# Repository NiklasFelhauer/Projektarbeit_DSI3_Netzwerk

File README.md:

# Projektarbeit_DSI3_Netzwerk
Umsetzung eines DSI3 Netzwerkes zwischen ESP32-Mikrocontrollern

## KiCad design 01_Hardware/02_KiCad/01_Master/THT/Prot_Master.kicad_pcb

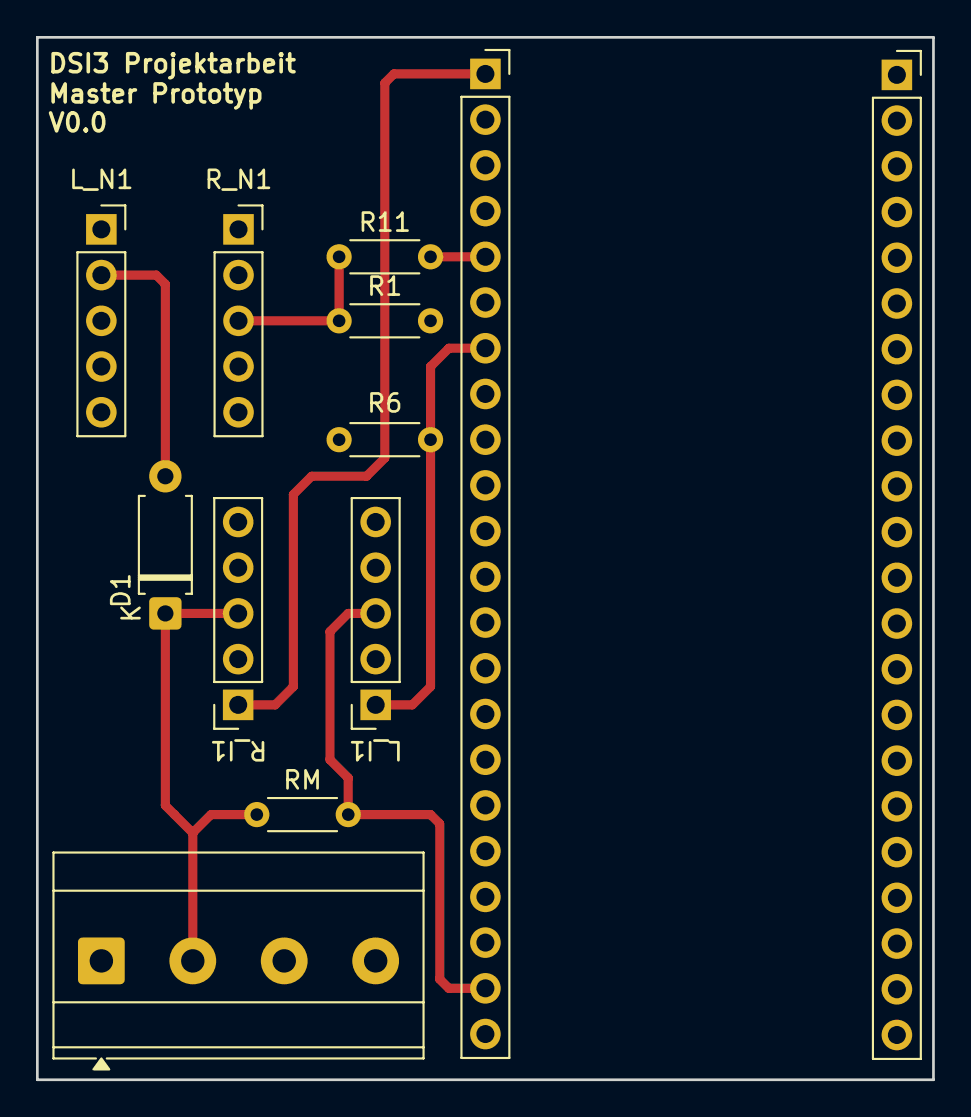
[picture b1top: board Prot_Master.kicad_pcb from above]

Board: 2 copper layers, 49.8 x 57.9 mm, 12 parts (0 on the bottom side), 8 nets.

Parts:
D1: BZX384xxxx; D_A-405_P7.62mm_Horizontal
J5: Screw_Terminal_01x04; TerminalBlock_Phoenix_MKDS-3-4-5.08_1x04_P5.08mm_Horizontal
J10, J20: Conn_01x22_Female; PinSocket_1x22_P2.54mm_Vertical
L_I1: NMOS1; PinSocket_1x05_P2.54mm_Vertical
L_N1: NMOS1; PinSocket_1x05_P2.54mm_Vertical
R1, R6: 10k; R_Axial_DIN0204_L3.6mm_D1.6mm_P5.08mm_Horizontal
R11: 33; R_Axial_DIN0204_L3.6mm_D1.6mm_P5.08mm_Horizontal
RM: 10; R_Axial_DIN0204_L3.6mm_D1.6mm_P5.08mm_Horizontal
R_I1: NMOS2; PinSocket_1x05_P2.54mm_Vertical
R_N1: NMOS1; PinSocket_1x05_P2.54mm_Vertical

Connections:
3.3V: J10.1, R_I1.1
5V: J10.21, L_I1.3, RM.2
Bus: D1.1 (K), J5.2, RM.1, R_I1.3
Drain_N1: D1.2 (A), L_N1.2 (Pin_2_2)
GND: J5.3, J10.22, L_I1.2, R1.2, R6.2, R_N1.1
GPIO: J10.7, L_I1.1, R6.1
Gate_N1: R1.1, R11.1, R_N1.3
unnamed: J10.5, R11.2

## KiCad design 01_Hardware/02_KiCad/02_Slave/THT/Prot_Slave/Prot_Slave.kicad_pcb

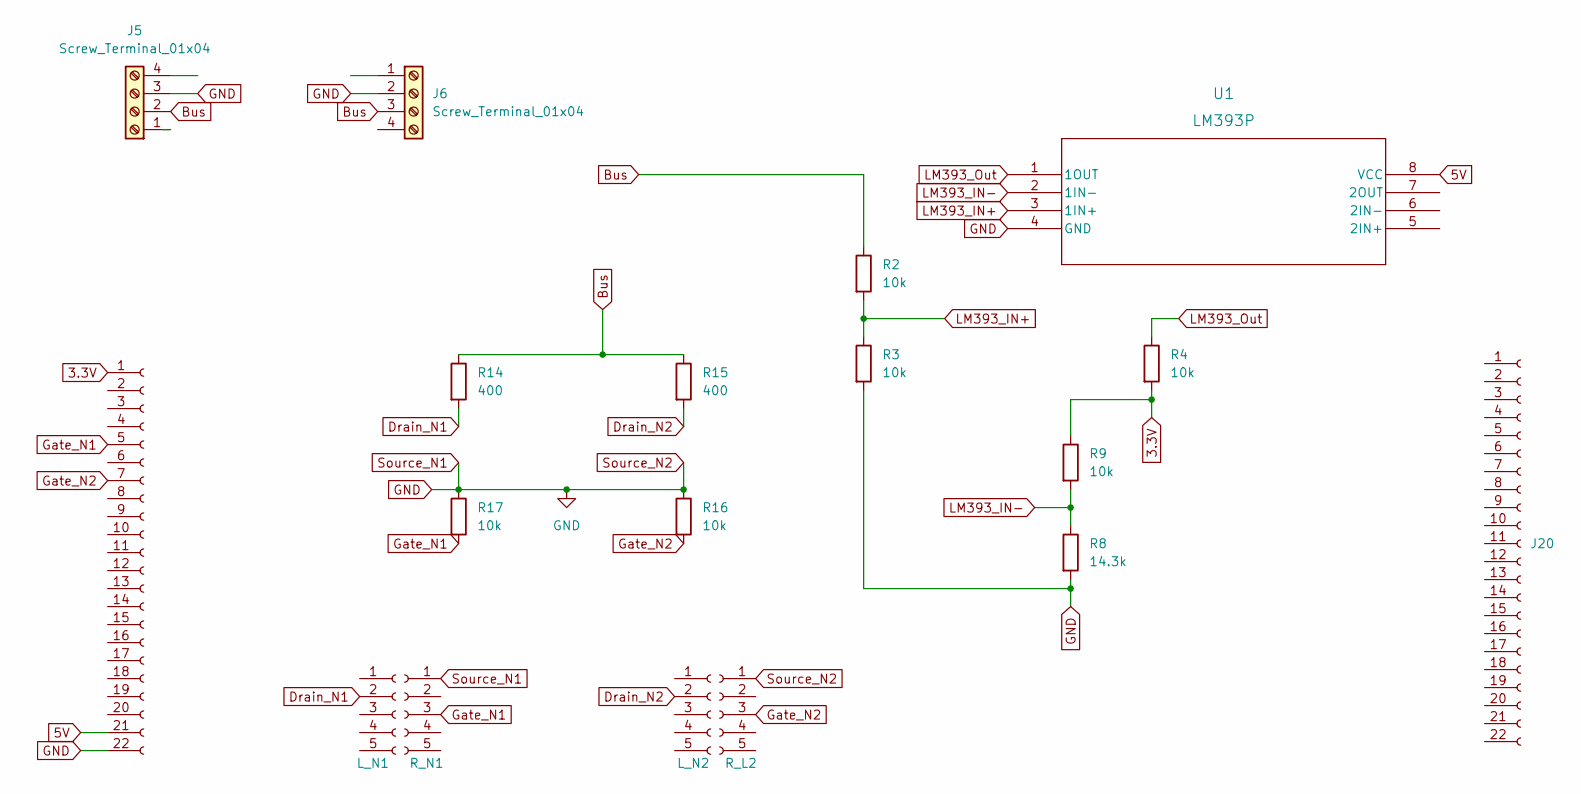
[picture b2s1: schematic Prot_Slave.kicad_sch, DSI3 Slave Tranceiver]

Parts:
J5, J6: Screw_Terminal_01x04; TerminalBlock_Phoenix_MKDS-3-4-5.08_1x04_P5.08mm_Horizontal
J10, J20: Conn_01x22_Female; PinSocket_1x22_P2.54mm_Vertical
L_N1, L_N2: NMOS1; PinSocket_1x05_P2.54mm_Vertical
R2, R3, R4, R9, R16, R17: 10k; R_Axial_DIN0204_L3.6mm_D1.6mm_P5.08mm_Horizontal
R8: 14.3k; R_Axial_DIN0204_L3.6mm_D1.6mm_P5.08mm_Horizontal
R14, R15: 400; R_Axial_DIN0204_L3.6mm_D1.6mm_P5.08mm_Horizontal
R_L2: NMOS2; PinSocket_1x05_P2.54mm_Vertical
R_N1: NMOS1; PinSocket_1x05_P2.54mm_Vertical
U1: LM393P; P8

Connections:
3.3V: J10.1, R4.2, R9.1
5V: J10.21, U1.8 (VCC)
Bus: J5.2, J6.3, R2.1, R14.1, R15.1
Drain_N1: L_N1.2 (Pin_2_2), R14.2
Drain_N2: L_N2.2 (Pin_2_2), R15.2
GND: J5.3, J6.2, J10.22, R3.2, R8.2, R16.1, R17.1, R_L2.1, R_N1.1, U1.4 (GND)
Gate_N1: J10.5, R17.2, R_N1.3
Gate_N2: J10.7, R16.2, R_L2.3
LM393_IN+: R2.2, R3.1, U1.3 (1IN+)
LM393_IN-: R8.1, R9.2, U1.2 (1IN-)
LM393_Out: R4.1, U1.1 (1OUT)

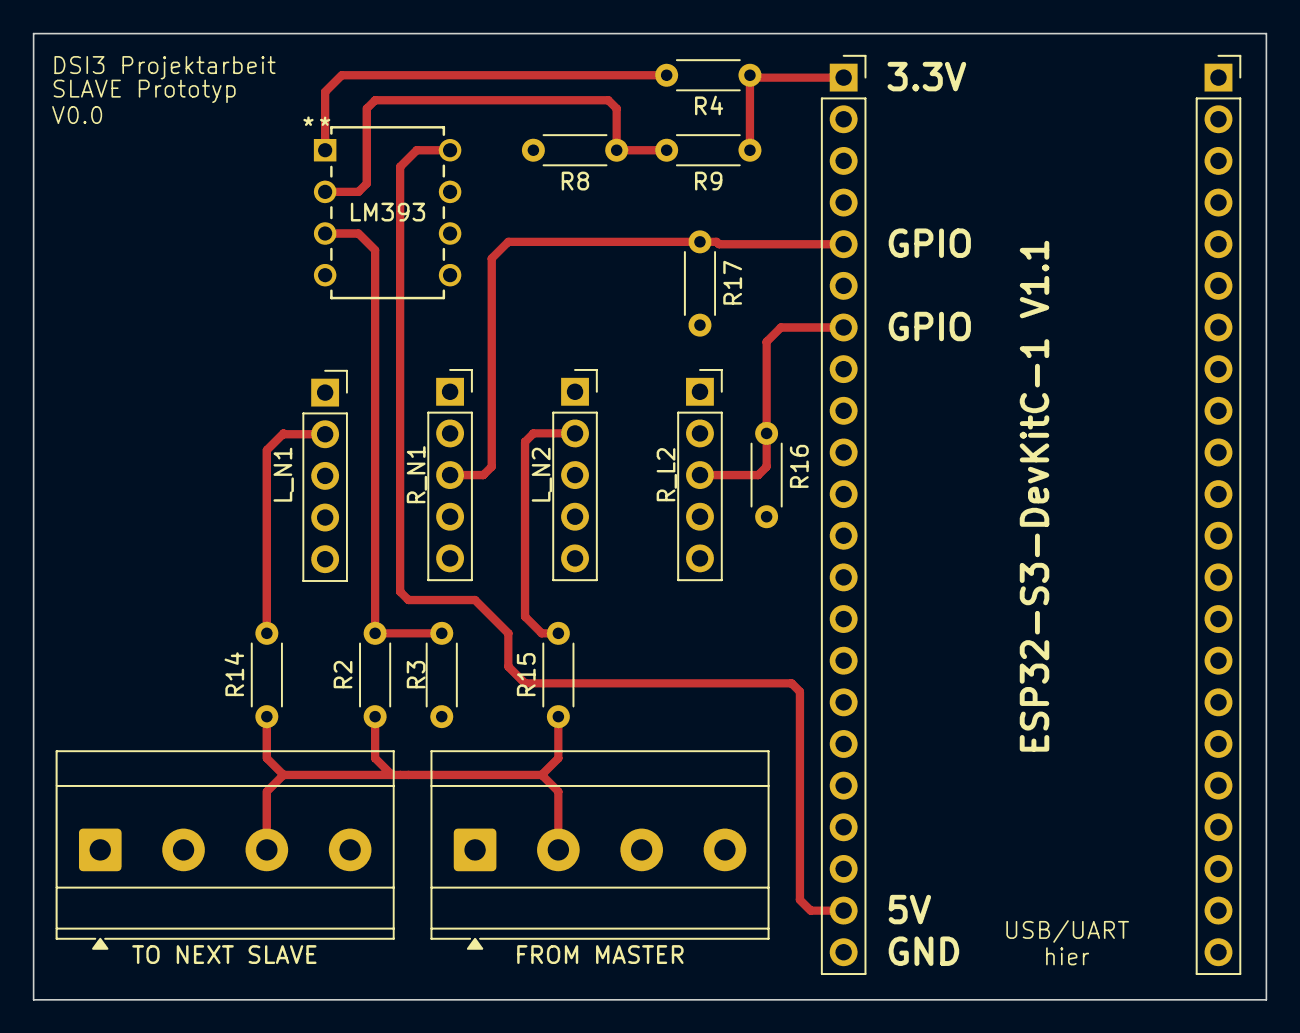
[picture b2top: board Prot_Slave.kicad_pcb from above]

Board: 2 copper layers, 75.2 x 58.9 mm, 18 parts (0 on the bottom side), 11 nets.

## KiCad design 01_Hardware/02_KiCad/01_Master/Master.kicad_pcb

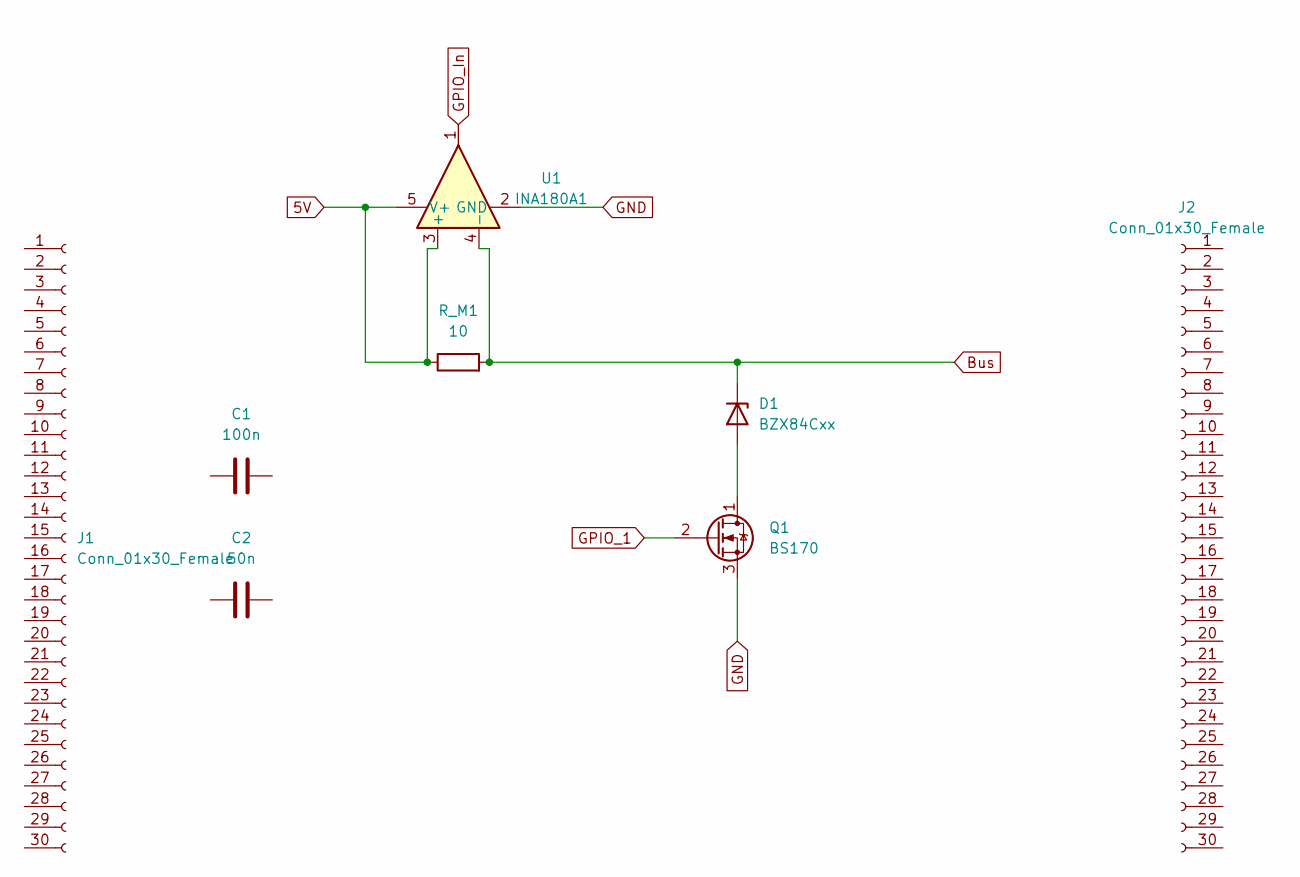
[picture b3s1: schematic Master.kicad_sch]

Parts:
C1: 100n; C_Axial_L3.8mm_D2.6mm_P7.50mm_Horizontal
C2: 50n; C_Axial_L3.8mm_D2.6mm_P7.50mm_Horizontal
D1: BZX84Cxx; SOT-23
J1, J2: Conn_01x30_Female; PinSocket_1x30_P2.54mm_Vertical
Q1: BS170; TO-92_Inline_Horizontal1
R_M1: 10; R_Axial_DIN0204_L3.6mm_D1.6mm_P5.08mm_Horizontal
U1: INA180A1; SOT-23-5

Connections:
5V: R_M1.1, U1.3 (+), U1.5 (V+)
Bus: D1.3 (K), R_M1.2, U1.4 (-)
GND: Q1.3 (S), U1.2 (GND)
GPIO_1: Q1.2 (G)
GPIO_In: U1.1
unnamed: D1.1 (A), Q1.1 (D)

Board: 2 copper layers, 8 parts (0 on the bottom side), 4 nets, no tracks yet.

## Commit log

2026-05-08 Initial
2026-05-08 Test
2026-05-08 Folder
2026-05-15 KiCAD
2026-05-15 KiCad V10
2026-05-15 Folder struc + HKA picture
2026-05-15 Slave KiCad 3D Draft
2026-05-15 KiCad Master draft
2026-05-15 FSM draft added
2026-05-16 ltspice documents added
2026-05-16 Folder structure updated
2026-06-04 KiCad Libraries added
2026-06-04 KiCad Slave Update, now routed
2026-06-05 Slave Zip
2026-06-05 KiCAD Update
2026-06-05 Master and Slave Prototyp finsished! JLCPCB ordered
2026-06-05 Unresolved files
2026-06-05 Gerber dir added
